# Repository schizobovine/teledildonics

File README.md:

# teledildonics
Software, firmware and hardware designs for sexy-action-at-a-distance.

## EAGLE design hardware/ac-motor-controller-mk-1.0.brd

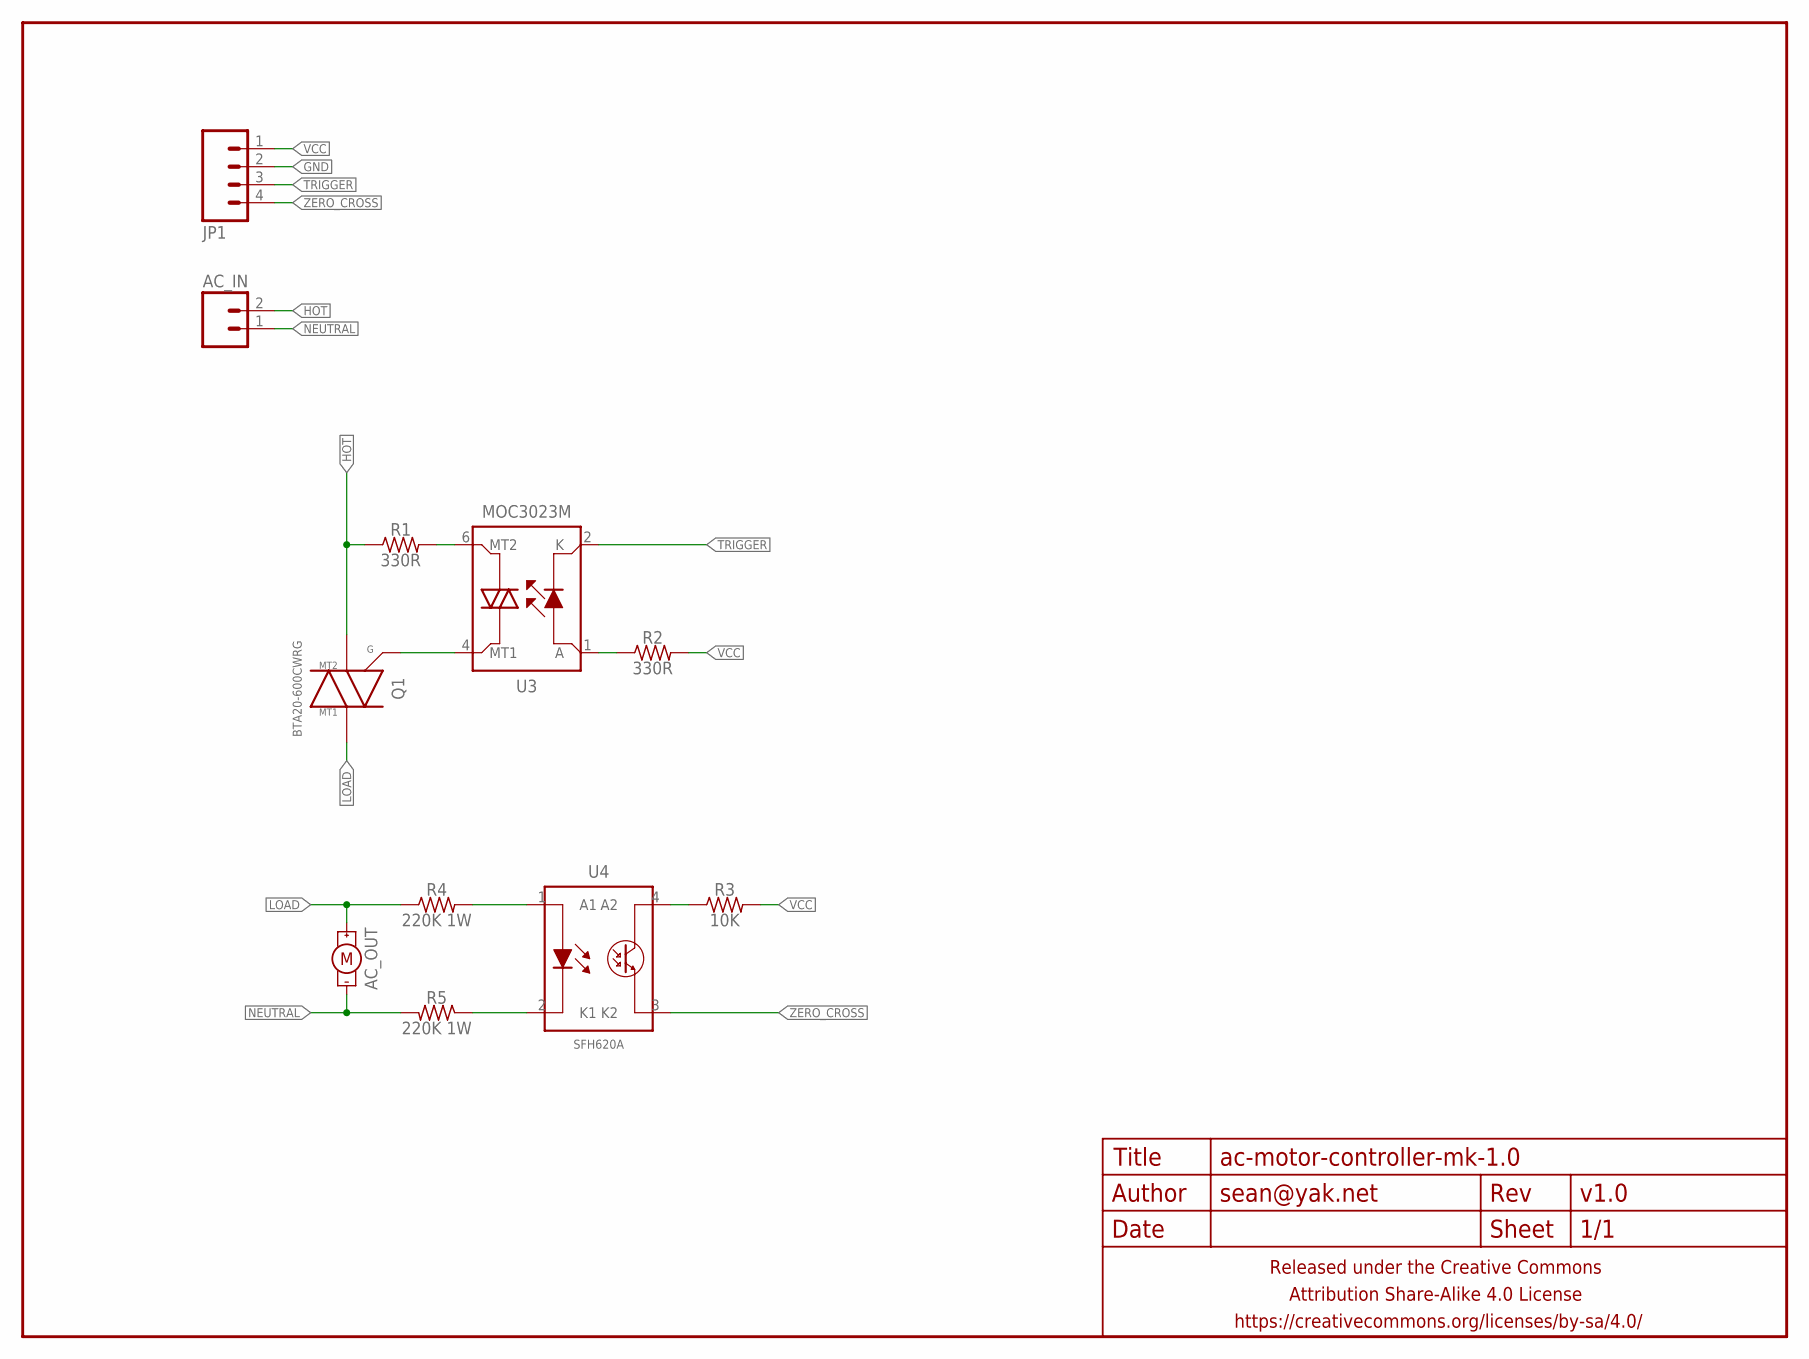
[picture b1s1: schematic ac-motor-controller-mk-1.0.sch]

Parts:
AC_IN: SCREWTERMINAL-25MM; SCREWTERM-5MM-2
AC_OUT: MOTOR5MM-SCREW-TERM; 1X02_5MM_SCREW
FRAME1: FRAME-LETTERNO_PACKAGE; DUMMY
JP1: M04JST-PTH-CENTERED; JST-4-PH-VERT-PTH-CENTERED
Q1: BTA20-600CWRG; TO220V
R1, R2: 330R; RESISTOR-AXIAL-PTH-5.08MM
R3: 10K; RESISTOR-AXIAL-PTH-5.08MM
R4, R5: 220K 1W; RESISTOR-AXIAL-PTH-10.16MM
U3: MOC3023M; DIP06
U4: SFH620A; DIL04

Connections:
GND: JP1.2
HOT: AC_IN.2, Q1.2 (MT2), R1.P$1 (1)
LOAD: AC_OUT.1 (+), Q1.1 (MT1), R4.P$1 (1)
unnamed: R4.P$2 (2), U4.1 (A1)
unnamed: R5.P$1 (1), U4.2 (K1)
unnamed: R1.P$2 (2), U3.6 (MT2)
unnamed: Q1.3 (GATE), U3.4 (MT1)
unnamed: R2.P$1 (1), U3.1 (A)
unnamed: R3.P$1 (1), U4.4 (A2)
NEUTRAL: AC_IN.1, AC_OUT.2 (-), R5.P$2 (2)
TRIGGER: JP1.3, U3.2 (K)
VCC: JP1.1, R2.P$2 (2), R3.P$2 (2)
ZERO_CROSS: JP1.4, U4.3 (K2)

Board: 2 copper layers, 12 parts (0 on the bottom side), 12 nets, no tracks yet.

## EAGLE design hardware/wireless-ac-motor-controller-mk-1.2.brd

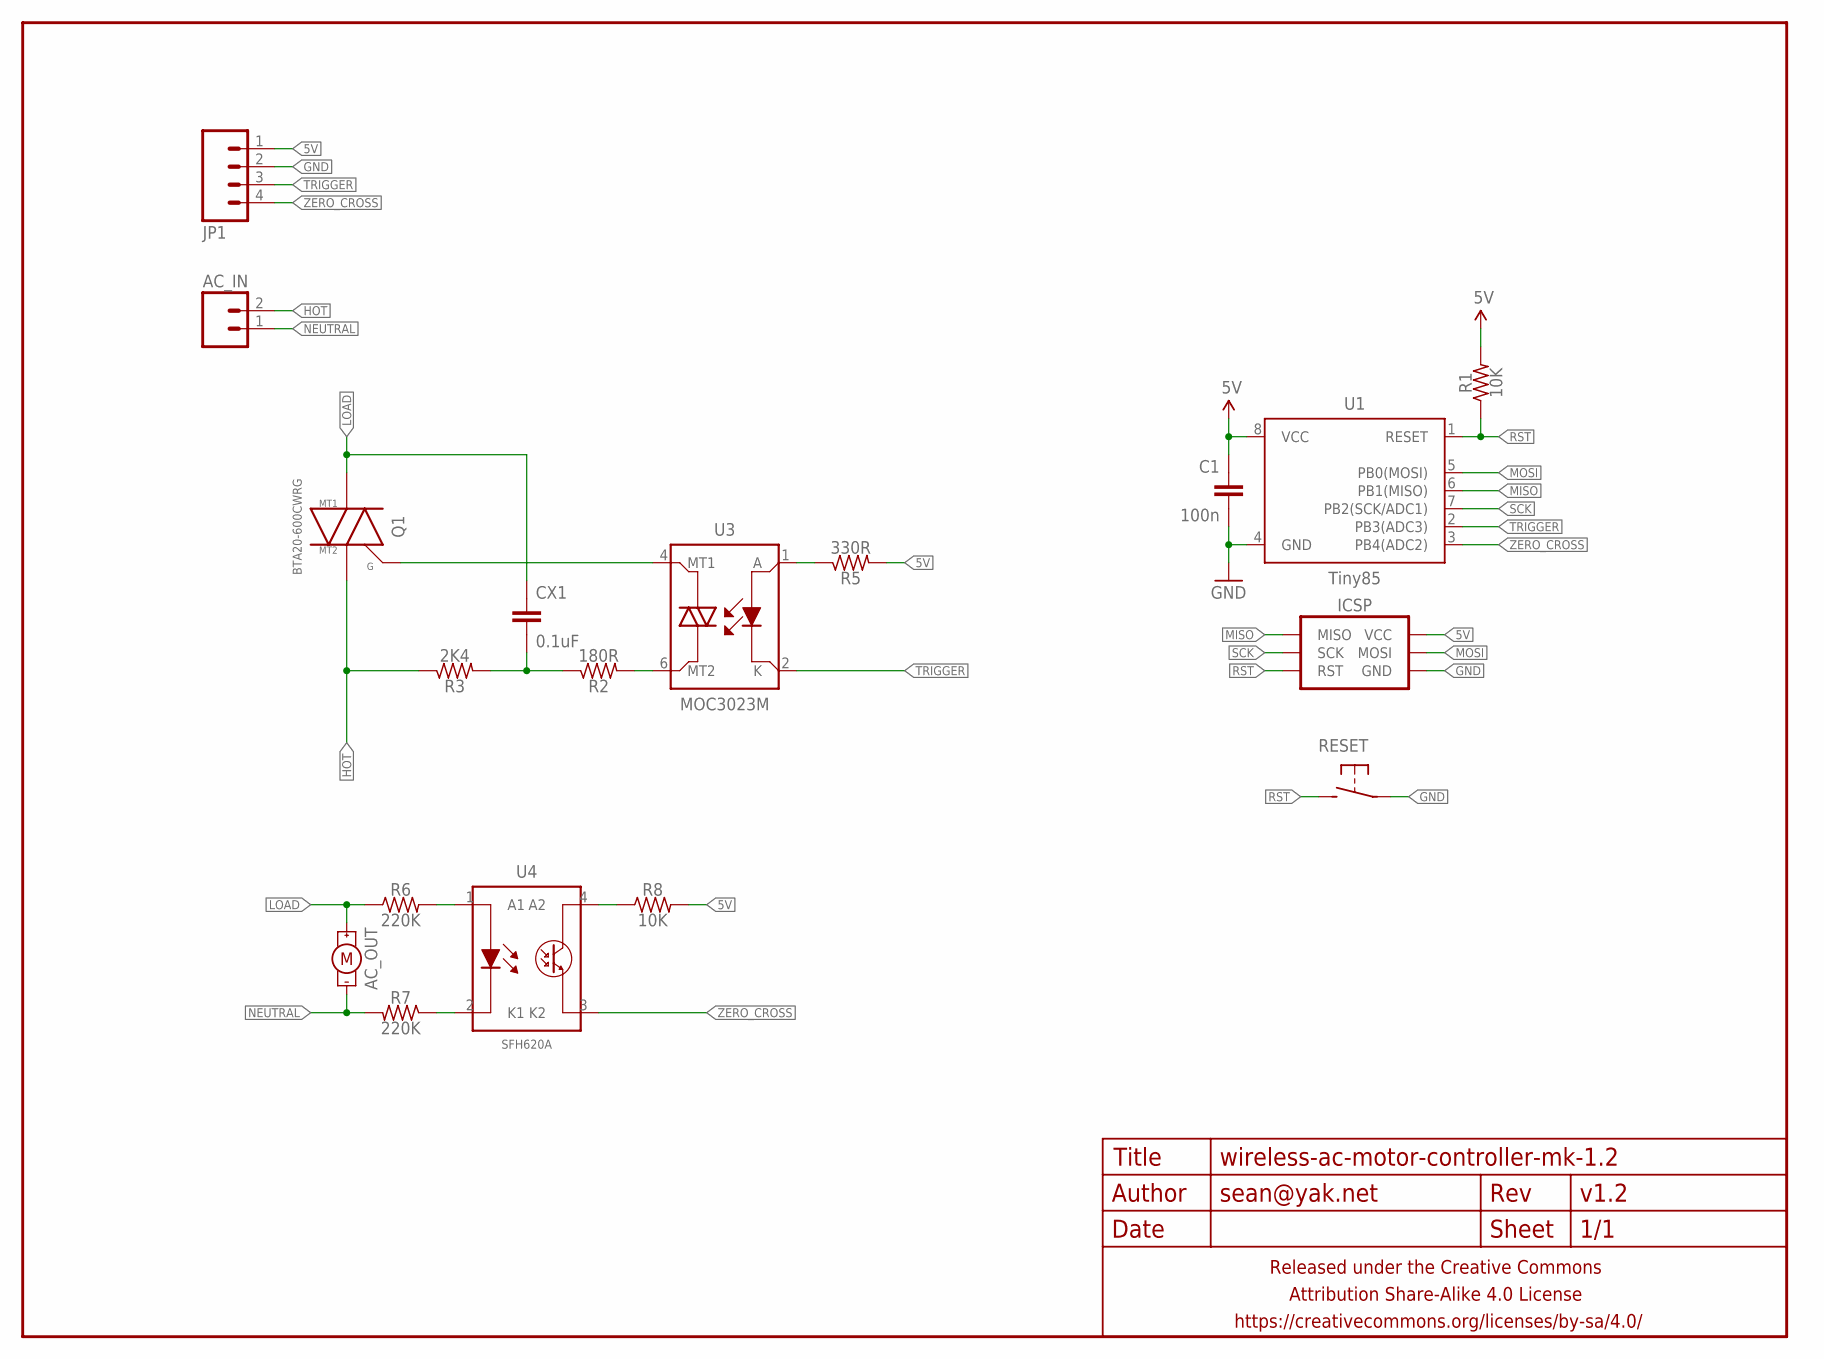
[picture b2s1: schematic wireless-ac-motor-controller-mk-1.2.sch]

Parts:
AC_IN: SCREWTERMINAL-25MM; SCREWTERM-5MM-2
AC_OUT: MOTOR5MM-SCREW-TERM; 1X02_5MM_SCREW
C1: 100n; C0805
CX1: 0.1uF; XC10B6
FRAME1: FRAME-LETTERNO_PACKAGE; DUMMY
ICSP: AVR_SPI_PRG_6PTH; 2X3
JP1: M04JST-PTH-VERT; JST-4-PH-VERT-PTH
Q1: BTA20-600CWRG; TO220V
R1, R8: 10K; R0805
R2: 180R; R0805
R3: 2K4; R0805
R5: 330R; R0805
R6, R7: 220K; 0411V
RESET: SPST-NO-TACT3MM-PTH-SMALL-PADS; DTS-3-SMALL-PADS
U1: Tiny85; SO08-EIAJ
U3: MOC3023M; DIP06
U4: SFH620A; DIL04

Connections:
5V: C1.1, ICSP.2 (VCC), JP1.1, R1.2, R5.2, R8.2, U1.8 (VCC)
GND: C1.2, ICSP.6 (GND), JP1.2, RESET.1, U1.4 (GND)
HOT: AC_IN.2, Q1.2 (MT2), R3.1
LOAD: AC_OUT.1 (+), CX1.1, Q1.1 (MT1), R6.1
MISO: ICSP.1 (MISO), U1.6 (PB1(MISO))
MOSI: ICSP.4 (MOSI), U1.5 (PB0(MOSI))
unnamed: R6.2, U4.1 (A1)
unnamed: R7.1, U4.2 (K1)
unnamed: R2.2, U3.6 (MT2)
unnamed: Q1.3 (GATE), U3.4 (MT1)
unnamed: CX1.2, R2.1, R3.2
unnamed: R5.1, U3.1 (A)
unnamed: R8.1, U4.4 (A2)
NEUTRAL: AC_IN.1, AC_OUT.2 (-), R7.2
RST: ICSP.5 (RST), R1.1, RESET.2, U1.1 (RESET)
SCK: ICSP.3 (SCK), U1.7 (PB2(SCK/ADC1))
TRIGGER: JP1.3, U1.2 (PB3(ADC3)), U3.2 (K)
ZERO_CROSS: JP1.4, U1.3 (PB4(ADC2)), U4.3 (K2)

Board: 2 copper layers, 19 parts (0 on the bottom side), 18 nets, no tracks yet.

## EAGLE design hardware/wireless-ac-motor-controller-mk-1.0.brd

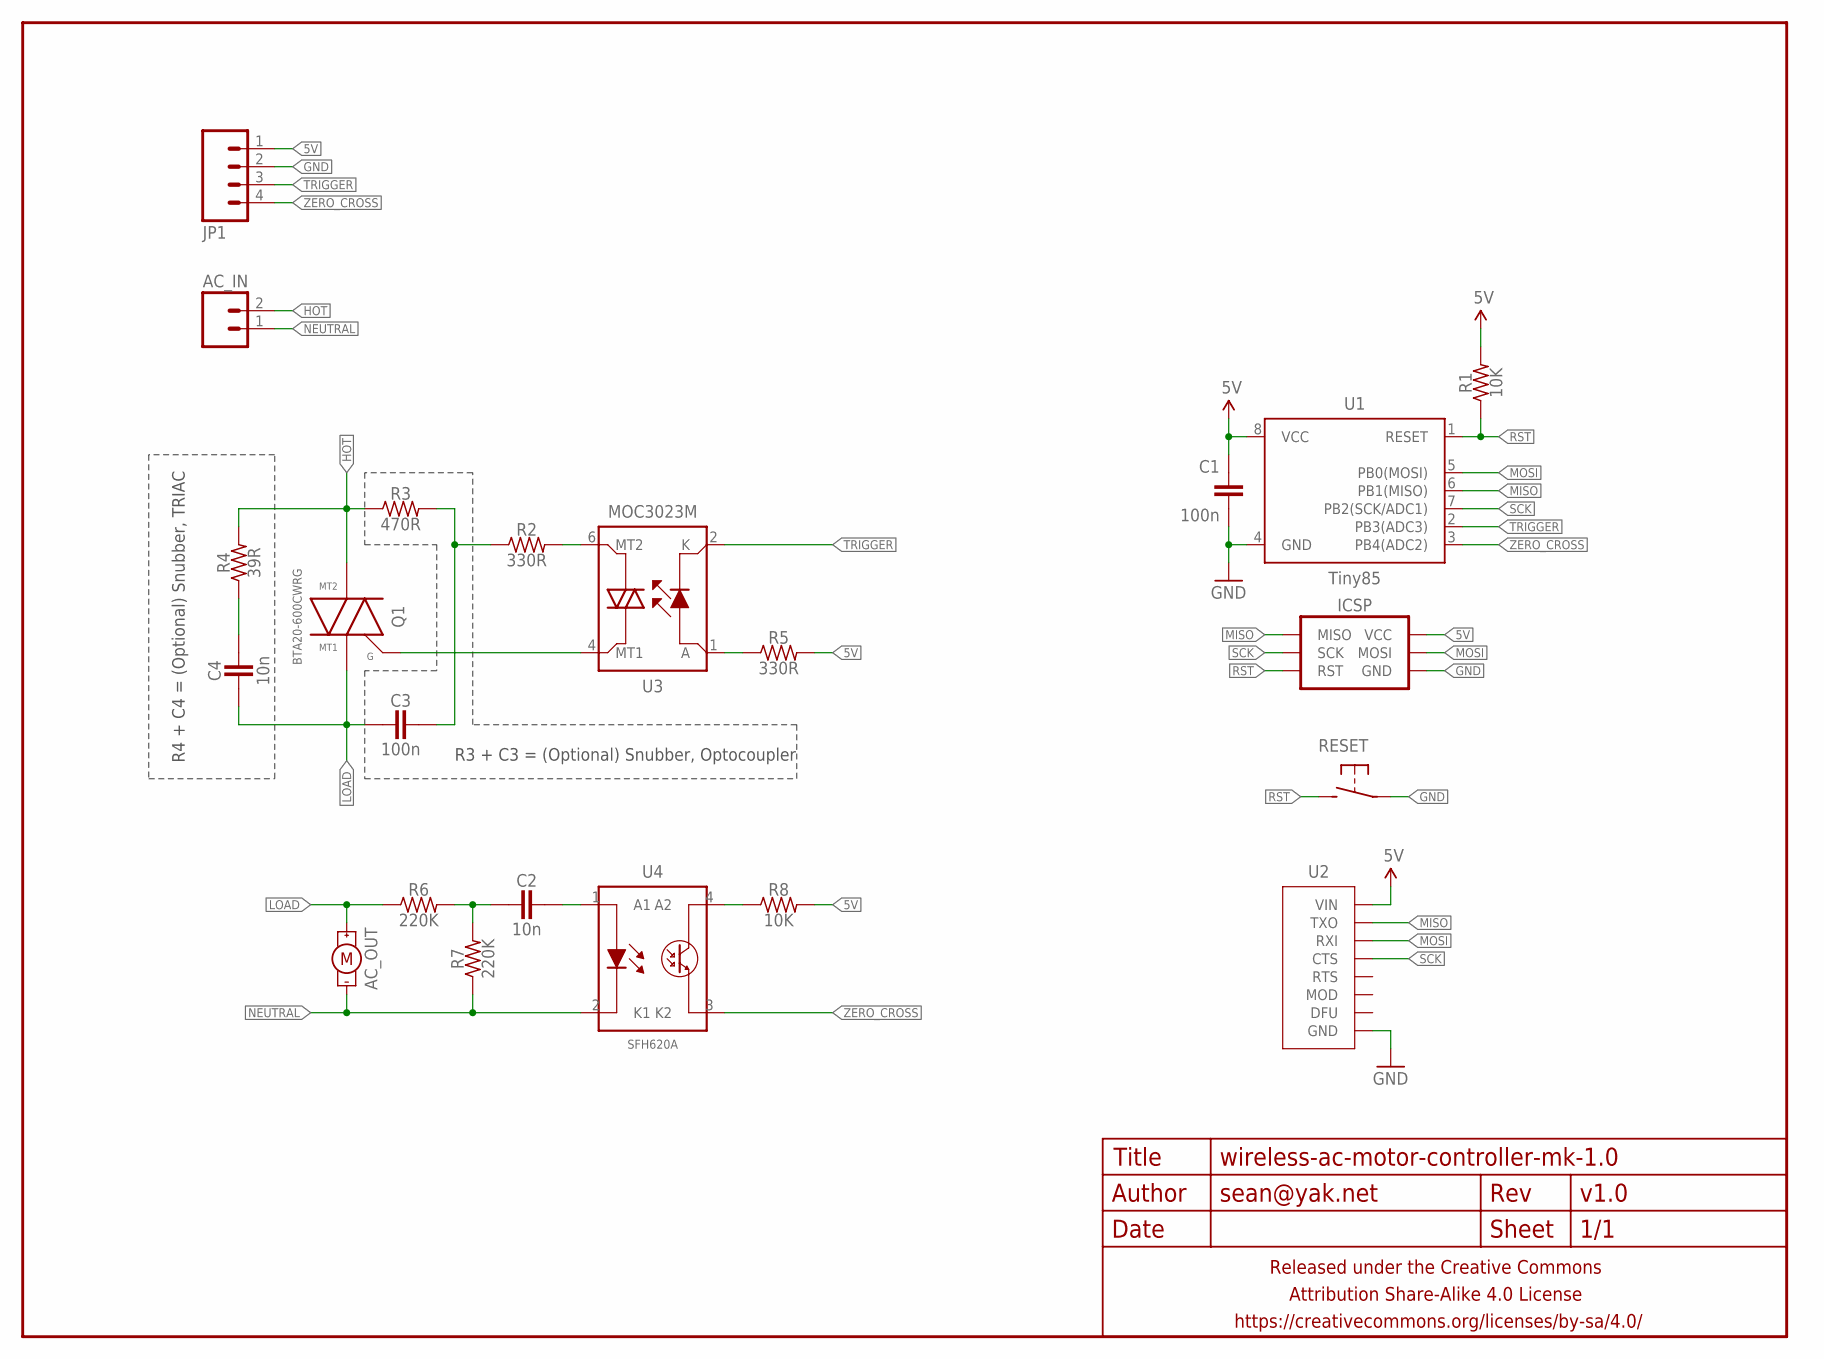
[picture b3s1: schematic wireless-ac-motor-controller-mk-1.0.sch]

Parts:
AC_IN: SCREWTERMINAL-25MM; SCREWTERM-5MM-2
AC_OUT: MOTOR5MM-SCREW-TERM; 1X02_5MM_SCREW
C1: 100n; C0805
C2: 10n; C0805
C3: 100n; C025-024X044
C4: 10n; C025-024X044
FRAME1: FRAME-LETTERNO_PACKAGE; DUMMY
ICSP: AVR_SPI_PRG_6PTH; 2X3
JP1: M04JST-PTH-VERT; JST-4-PH-VERT-PTH
Q1: BTA20-600CWRG; TO220V
R1: 10K; R0805
R2: 330R; RESISTOR-AXIAL-PTH-5.08MM
R3: 470R; RESISTOR-AXIAL-PTH-7.62MM
R4: 39R; RESISTOR-AXIAL-PTH-7.62MM
R5: 330R; R0805
R6, R7: 220K; RESISTOR-AXIAL-PTH-6.35MM
R8: 10K; RESISTOR-AXIAL-PTH-7.62MM
RESET: SPST-NO-TACT3MM-PTH-SMALL-PADS; DTS-3-SMALL-PADS
U1: Tiny85; SO08-EIAJ
U2: ADAFRUIT_BLE_UARTBARE; ADAFRUIT_BLE_UART
U3: MOC3023M; DIP06
U4: SFH620A; DIL04

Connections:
5V: C1.1, ICSP.2 (VCC), JP1.1, R1.2, R5.2, R8.P$2 (2), U1.8 (VCC), U2.VIN
GND: C1.2, ICSP.6 (GND), JP1.2, RESET.1, U1.4 (GND), U2.GND
HOT: AC_IN.2, Q1.2 (MT2), R3.P$1 (1), R4.P$2 (2)
LOAD: AC_OUT.1 (+), C3.2, C4.2, Q1.1 (MT1), R6.P$1 (1)
MISO: ICSP.1 (MISO), U1.6 (PB1(MISO)), U2.TXO
MOSI: ICSP.4 (MOSI), U1.5 (PB0(MOSI)), U2.RXI
unnamed: C2.2, R6.P$2 (2), R7.P$2 (2)
unnamed: C3.1, R2.P$1 (1), R3.P$2 (2)
unnamed: R2.P$2 (2), U3.6 (MT2)
unnamed: Q1.3 (GATE), U3.4 (MT1)
unnamed: C4.1, R4.P$1 (1)
unnamed: R5.1, U3.1 (A)
unnamed: C2.1, U4.1 (A1)
unnamed: R8.P$1 (1), U4.4 (A2)
NEUTRAL: AC_IN.1, AC_OUT.2 (-), R7.P$1 (1), U4.2 (K1)
RST: ICSP.5 (RST), R1.1, RESET.2, U1.1 (RESET)
SCK: ICSP.3 (SCK), U1.7 (PB2(SCK/ADC1)), U2.CTS
TRIGGER: JP1.3, U1.2 (PB3(ADC3)), U3.2 (K)
ZERO_CROSS: JP1.4, U1.3 (PB4(ADC2)), U4.3 (K2)

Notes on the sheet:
R3 + C3 = (Optional) Snubber, Optocoupler
R4 + C4 = (Optional) Snubber, TRIAC

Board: 2 copper layers, 23 parts (0 on the bottom side), 19 nets, no tracks yet.

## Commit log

2015-12-21 initial checkin and structure
2018-03-19 attempt at ble controlled hitachi

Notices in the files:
parts and their libraries:
a_parts: Released under the Creative Commons Attribution Share-Alike 4.0 License
a_parts: https://creativecommons.org/licenses/by-sa/4.0
a_parts: Released under the Creative Commons
